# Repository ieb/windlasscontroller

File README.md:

# Windlass Remote Control

I have found that wire windlass switches fail at when installed at the bow due to water ingress into the switches as do sockets. So 7 years ago I used a simple 433Mhz garage door controller as a remote windlass controller. However the remote controls are not easy to use being too small, and the range is typically less than 10m which is shorter than the boat making the controller unreliable.

This project uses a JDY-40 module (typical cost < $1) which can be configured as a remote 8 channel switch. It has a claimed range of 120m, tested at 60m and uses 2.4GHz. It sleeps automatically drawing 5uA when sleeping and requires almost no external components in the controller. The base uses a second JDY-40 module with opto couplers and a G1 transistor driving a relay.  Remote is powered by a CR123A 3V lithium battery which should last several years even if left on sleeping. There is an on-off switch. No custom code, but the modules have to be programmed as transmitter and base with the same RF IDs. Code to do this is in setup. 

There are 2 schematics, one for base and one for the controller, and designs for the case and base cases. 

The PCBs are in KiCad, and were milled using pcb2gcode double sided with alignment, see createGCode.sh for the setup. Everything else is very standard.

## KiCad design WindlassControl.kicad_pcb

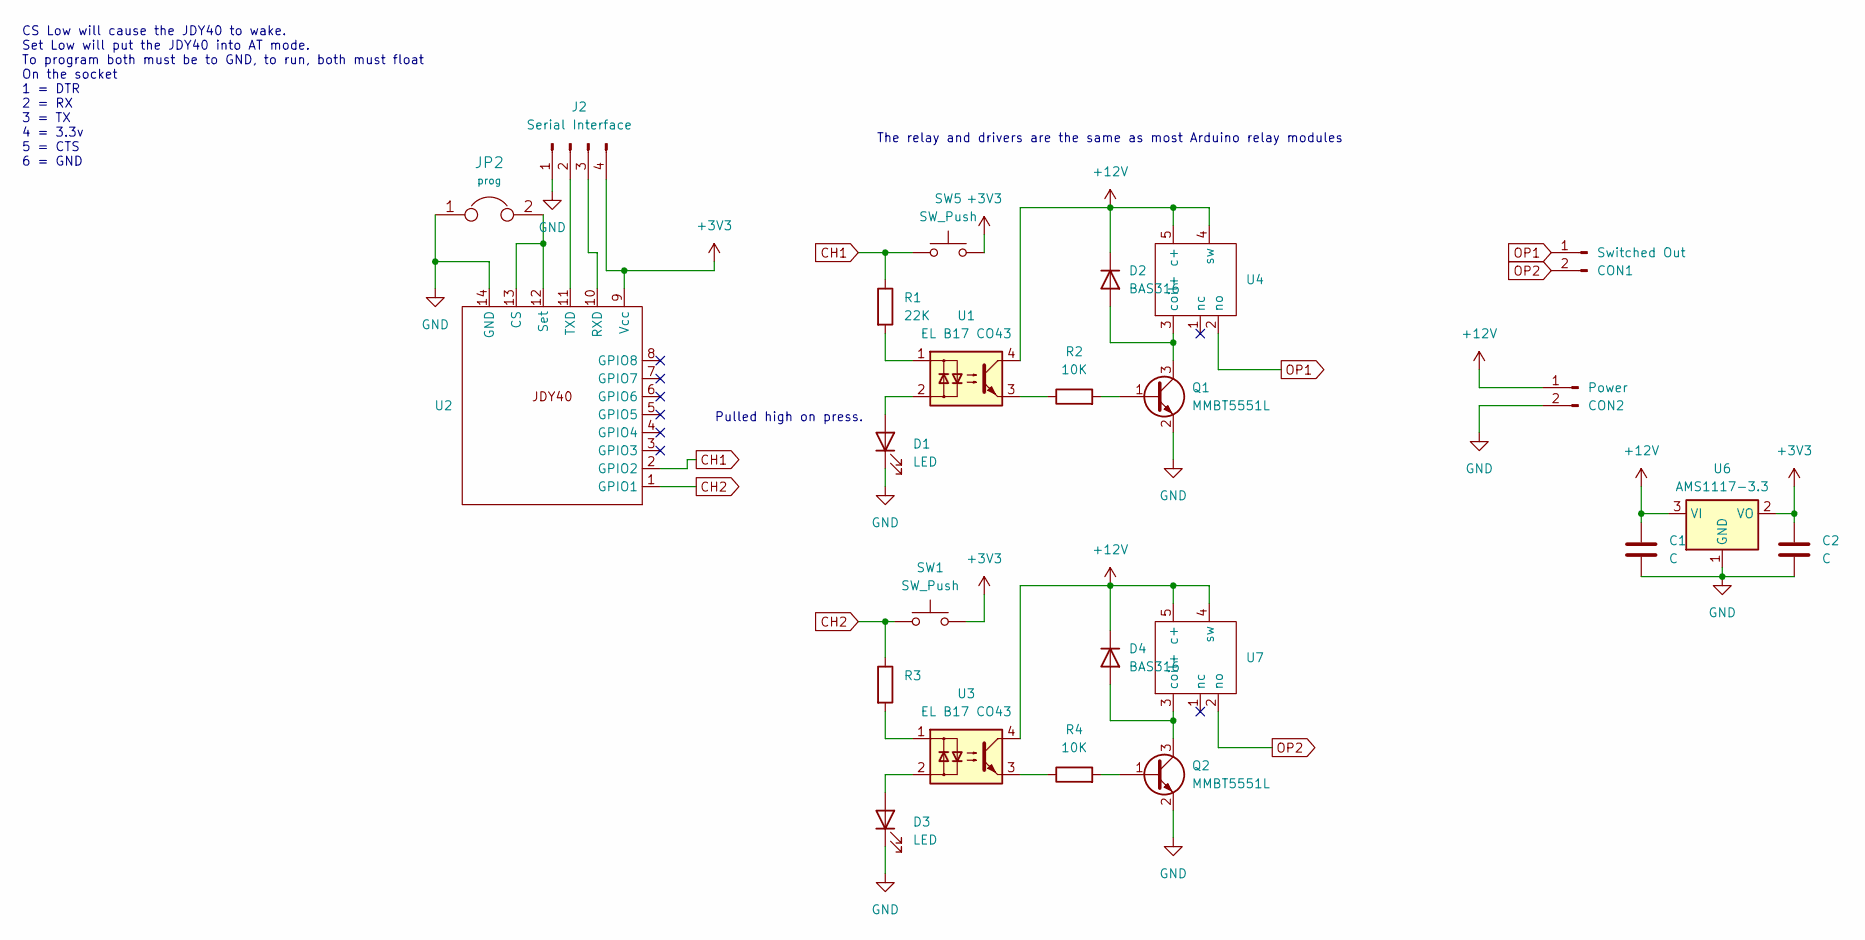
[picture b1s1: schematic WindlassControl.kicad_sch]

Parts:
C1, C2: C; C_1210_3225Metric
CON1: Switched Out; Molex_KK-396_5273-02A_1x02_P3.96mm_Vertical
CON2: Power; Molex_KK-396_5273-02A_1x02_P3.96mm_Vertical
D1: LED; LED_0805_2012Metric_Pad1.15x1.40mm_HandSolder
D2, D4: BAS316; LED_1206_3216Metric_Pad1.42x1.75mm_HandSolder
D3: LED; LED_0805_2012Metric
J2: Serial Interface; Harwin_M20-89004xx_1x04_P2.54mm_Horizontal
JP2: prog; SolderJumper-2_P1.3mm_Open_Pad1.0x1.5mm
Q1, Q2: MMBT5551L; SOT-23
R1: 22K; R_0805_2012Metric_Pad1.20x1.40mm_HandSolder
R2, R4: 10K; R_0805_2012Metric_Pad1.20x1.40mm_HandSolder
R3: 2.2K; R_0805_2012Metric_Pad1.20x1.40mm_HandSolder
SW1, SW5: SW_Push; SW_SPST_EVPBF
U1, U3: EL B17 CO43; OptoIsoator4pin
U2: Jdy40
U4, U7: Relay Tongling
U6: AMS1117-3.3; SOT-223-3_TabPin2

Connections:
+3V3: C2.1, J2.4, SW1.2, SW5.2, U2.9 (Vcc), U6.2 (VO)
+12V: C1.1, CON2.1, D2.1 (K), D4.1 (K), U1.4, U3.4, U4.4 (sw), U4.5 (c+), U6.3 (VI), U7.4 (sw), U7.5 (c+)
CH1: R1.1, SW5.1, U2.2 (GPIO2)
CH2: R3.1, SW1.1, U2.1 (GPIO1)
GND: C1.2, C2.2, CON2.2, D1.1 (K), D3.1 (K), J2.1, JP2.1, Q1.2 (E), Q2.2 (E), U2.14 (GND), U6.1 (GND)
unnamed: D1.2 (A), U1.2
unnamed: D2.2 (A), Q1.3 (C), U4.3 (coil+)
unnamed: D3.2 (A), U3.2
unnamed: D4.2 (A), Q2.3 (C), U7.3 (coil+)
unnamed: J2.2, U2.11 (TXD)
unnamed: J2.3, U2.10 (RXD)
unnamed: Q1.1 (B), R2.2
unnamed: Q2.1 (B), R4.2
unnamed: R1.2, U1.1
unnamed: R2.1, U1.3
unnamed: R3.2, U3.1
unnamed: R4.1, U3.3
unnamed: JP2.2, U2.12 (Set), U2.13 (CS)
OP1: CON1.1, U4.2 (no)
OP2: CON1.2, U7.2 (no)

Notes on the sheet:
The relay and drivers are the same as most Arduino relay modules
CS Low will cause the JDY40 to wake. Set Low will put the JDY40 into AT mode. To program both must be to GND, to run, both must float On the socket 1 = DTR 2 = RX 3 = TX 4 = 3.3v 5 = CTS 6 = GND
Pulled high on press.

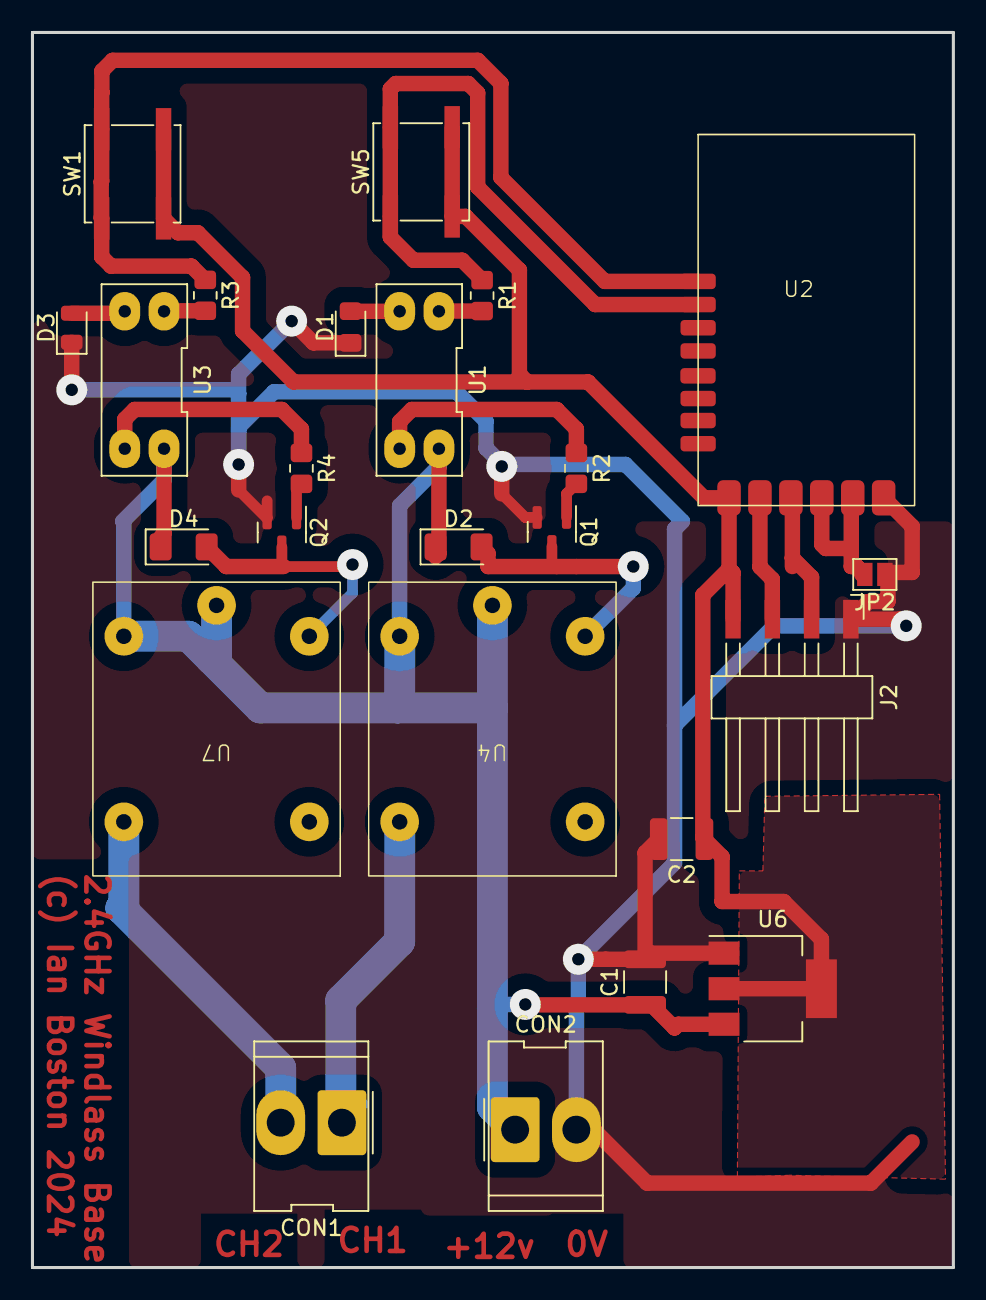
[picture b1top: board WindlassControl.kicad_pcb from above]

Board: 2 copper layers, 59.6 x 79.9 mm, 24 parts (0 on the bottom side), 20 nets.

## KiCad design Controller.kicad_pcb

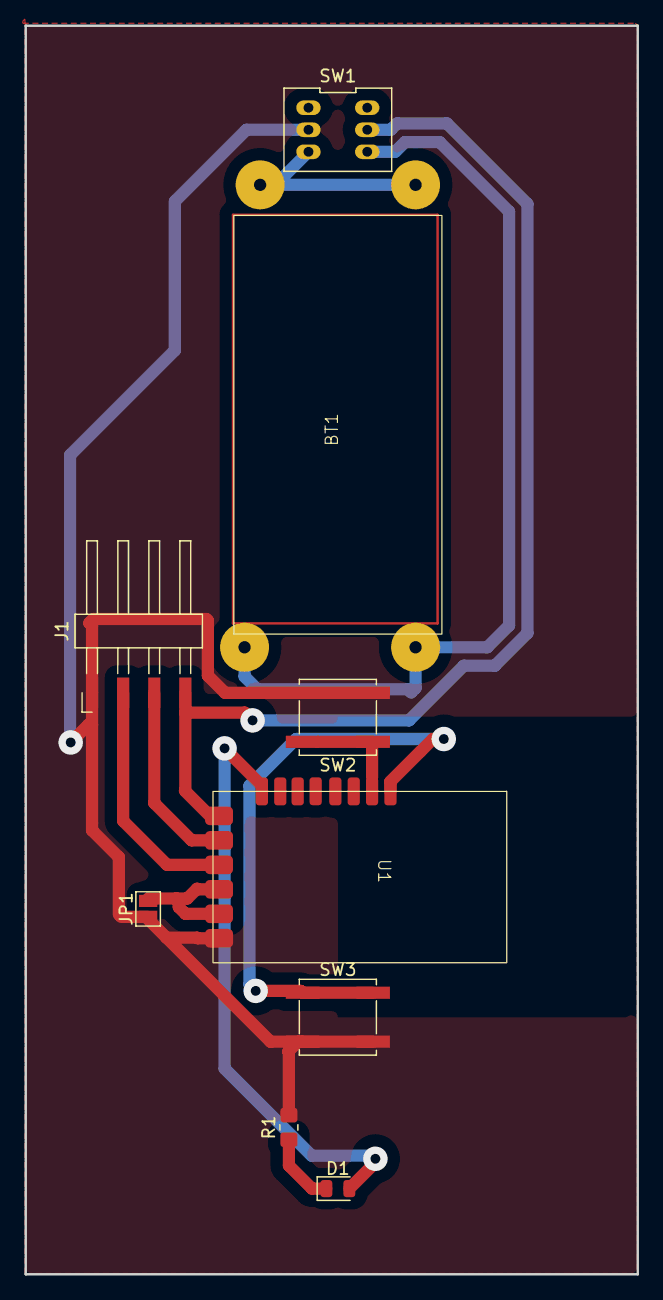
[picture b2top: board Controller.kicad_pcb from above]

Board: 2 copper layers, 50.0 x 102.0 mm, 9 parts (0 on the bottom side), 11 nets.

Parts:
BT1: CR123 3V Lithium battery; CR123AHolder
D1: LED; LED_0805_2012Metric
J1: Serial Interface; Harwin_M20-89004xx_1x04_P2.54mm_Horizontal
JP1: prog; SolderJumper-2_P1.3mm_Open_Pad1.0x1.5mm
R1: 1K; R_0805_2012Metric_Pad1.20x1.40mm_HandSolder
SW1: SW_Push_DPDT; DPDT Latch Push 7x7
SW2, SW3: SW_Push; SW_SPST_EVPBF
U1: Jdy40

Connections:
Batt+: J1.4, SW1.5 (B), U1.9 (Vcc)
Batt-: J1.1, JP1.1, R1.2, SW1.2 (B), SW2.2, SW3.2, U1.14 (GND)
unnamed: BT1.1 (+), SW1.6 (C)
unnamed: BT1.2 (-), SW1.3 (C)
unnamed: D1.2 (A), U1.8 (GPIO8)
unnamed: D1.1 (K), R1.1
unnamed: J1.2, U1.11 (TXD)
unnamed: J1.3, U1.10 (RXD)
unnamed: JP1.2, U1.12 (Set), U1.13 (CS)
unnamed: SW3.1, U1.1 (GPIO1)
unnamed: SW2.1, U1.2 (GPIO2)

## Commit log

2024-06-05 Working devices
